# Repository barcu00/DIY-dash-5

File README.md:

# DIY Dash 5

DIY Dash 5 is an open, configurable auxiliary CAN dashboard for motorsport and
road cars. It is designed for the **Waveshare ESP32-S3-Touch-LCD-5 non-B**
board with an 800 × 480 RGB display, GT911 touch controller, 16 MB flash, and
8 MB OPI PSRAM.

The dashboard does not replace the factory instrument cluster. It adds a
dedicated screen for engine, ECU, and vehicle data, configurable warnings,
temperature status, and a track-oriented shift light. CAN operation is passive
and receive-only.

## Current firmware

The current test-board release is **v0.2.1**.

- [Open the v0.2.1 release](https://github.com/barcu00/DIY-dash-5/releases/tag/v0.2.1)
- [Download the complete 16 MB flash image](https://github.com/barcu00/DIY-dash-5/releases/download/v0.2.1/DIY-Dash-ESP32-S3-Touch-LCD-5-full.bin)
- [View the validated GitHub Actions build](https://github.com/barcu00/DIY-dash-5/actions/runs/34399159652)

Flash the complete image at address **`0x0`**. Its expected SHA-256 is:

```text
9FC9DD483754B7DDDF8EE3D20B1D87F31489FC43DA1D19DF0F165997BE9AAF70
```

> [!IMPORTANT]
> v0.2.1 is a prerelease for a physical test board. Automated tests verify the
> software, UI previews, ESP32-S3 compilation, and binary packaging. Vehicle
> wiring, touch response, CAN traffic, temperature, and long-duration stability
> still require validation on the actual installation.

## Development firmware: required storage migration

The current development build stores the complete dashboard configuration in
the dedicated **`dashcfg`** NVS partition. It is **512 KiB**, separate from the
small system NVS partition used by the ESP32 and Bluetooth stack. Every save is
read back byte-for-byte before the active configuration is changed.

This partition layout must be installed once with the merged image. Download
`DIY-Dash-ESP32-S3-Touch-LCD-5-full.bin` from the matching successful GitHub
Actions run and **flash at 0x0**. Installing this full image replaces the old
partition table and **clears existing settings**; configure the dashboard again
after the first boot. Do not install this migration using `firmware.bin` alone.
Later source builds remain fully compilable with PlatformIO as described below.

BACK, DASH, and TRACK all use the same deferred, verified save path. A failed
save keeps the current screen usable and shows `EXIT WITHOUT SAVE`, so the
driver can discard the draft instead of becoming trapped in `SAVE ERROR`.
RaceChrono now uses a 64 × 32 switch and separate status lines, including
`BLE: WAITING FOR APP`, `DATA: WAITING`/`DATA: ACTIVE`, and `GPS: NO FIX`.

## Interface preview

### Development: original selectable layouts

The `dashboard-dev` branch adds **Classic DASH, Classic TRACK, Analog Style,
Side Gear, and Strip Style**; newer builds add OEM Sport, Track Focus,
Endurance, Analog Classic, and Analog Twin (Modern Motorsport was removed in
configuration schema 12). In SETTINGS the layouts are now named FULL GRID,
TRACK GRID, DIAL + ROWS, GEAR LEFT, ARC STRIP, ROAD SPORT, LAP TIMER,
ENDURANCE, GAUGES and TWIN DIALS (same order as the names above). This is newer than the published v0.2.1 BIN above;
it is not yet a released firmware.

In `SETTINGS > LAYOUTS`, assign any preset independently to DASH and TRACK.
Each page retains its own tile settings for every preset. The shared
`RPM SCALE MAX` slider controls both pages from 100 to 10,000 RPM in 100-RPM
steps and does not change shift-light thresholds. Changes save on screen exit.
Hidden tiles compact within their group; holding a tile opens the existing
full-screen editor. Navigation includes gauge, checkered flag, and gear icons.

The development layouts below are **real production-view LVGL 8.4
framebuffer captures**, rendered on GitHub with the firmware's TileView,
RpmScaleView, ShiftLightView and navigation code. No UI reconstruction is used.
Black panels, condensed white digits, fine blue-grey frames and cyan navigation
follow the approved visual prototypes. Analog D uses a colored ring, a moving
white rectangular index and a configurable center tile (RPM by default).
Hold the center tile to choose a parameter, visibility and warning settings;
the ring and index always remain RPM-driven. At the flash threshold, the entire
segmented ring flashes red/dim at 4 Hz while the index remains white.
Side Gear
shares one RPM/speed frame; Strip uses identical upright rectangular blocks without a logo.
Tile rails and frames are neutral grey, compact-row labels and values are optically centered, and
scale labels always use whole thousands. Physical performance still needs board testing.

| Analog Style | Side Gear | Strip Style |
| --- | --- | --- |
|  |  |  |

| DASH | TRACK |
| --- | --- |
|  |  |

The [production preview workflow](.github/workflows/production-view-previews.yml)
checks 18 scenes, including flags, warning borders, 6000/7500/10000 RPM, red flash
phases and unavailable captions. It compares incremental redraws against full
framebuffers for Analog, Side Gear and Strip, including small
RPM changes and validity transitions. Its artifacts provide all captured scenes.
Configuration schema v8 migrates v6/v7 settings while retaining the original
layout banks and warning-sound preference; the new layout starts with its own defaults.
The display now uses two complete RGB framebuffers with VSYNC-controlled swaps,
and a 512 KiB LVGL pool in PSRAM.
Returning from settings or a successful tile save prepares the destination
layout and current values before displaying it, avoiding a stale first frame.
See [UI transition and Analog validation](docs/ui/ui-transition-validation.md)
for the successful build, full-image checksum and flashing precautions.
The newer [RGB/NVS XIP test candidate](docs/ui/rgb-nvs-xip-validation.md)
uses the official Arduino 3.1.1-h SDK libraries to support RGB bounce-buffer
operation during flash saves. Its GitHub tests and target build passed; physical
save-time stability still requires board testing. SDK selection is automatic
through `platformio.ini`, with compile-time checks against incompatible libraries.
### Development: tabbed editor and shared RPM settings

The new full-screen editor offers DATA, WARNING and temperature-only TEMPERATURE
BAR tabs, a large numeric keypad, and a categorized capability-filtered parameter
picker. Warning settings use an explicit RESET BELOW/ABOVE boundary. Untouched
fields retain native precision when saving in PSI, kPa or Fahrenheit.
TEST WARNING previews the modal and optionally pulses the buzzer without changing
actual alarms. RPM & SHIFT LIGHT combines the shared scale, color/flash thresholds,
a clearly labelled `12-LED FILL MAX` slider and one FLASH ENABLED switch. Fill max
sets the RPM at which all 12 segments are lit; it is no longer an isolated lower-right
field. Settings still save on exit;
tile drafts commit only after successful storage. SDK XIP and VSYNC buffering remain unchanged.

These are **actual production LVGL captures**, validated in direct and partial
render modes. See [candidate tests, checksum and hardware checklist](docs/ui/tile-editor-rpm-validation.md).

| DATA | WARNING | TEMPERATURE BAR |
| --- | --- | --- |
|  |  |  |

| NUMERIC ENTRY | PARAMETER PICKER | RPM & SHIFT LIGHT |
| --- | --- | --- |
|  |  |  |

The settings/flag/modal illustrations below remain older geometry previews,
not current production editor captures.

| SETTINGS | TILE SETTINGS |
| --- | --- |
|  |  |

| STATUS FLAGS | WARNING MODAL |
| --- | --- |
|  |  |

The real layout captures and earlier geometry previews are available in
[`docs/ui/screenshots`](docs/ui/screenshots).

## Main features

### RaceChrono Bluetooth LE monitor (development)

The development firmware advertises as **`DIY DASH RC`** and implements the
RaceChrono DIY Monitor service `0x1FF8`. Enable it under
`SETTINGS > DATA & CAN > RACECHRONO`; the full-screen `CONNECTION` and
`CHANNELS` pages show live BLE/GPS state and all 33 supplemental channels.
**CAN / DEMO remains active** while RaceChrono adds lap time, live delta,
comparison/reference time, sector, GPS, satellite, accuracy, position, and
acceleration data. RaceChrono values can be selected for any compatible tile
even while the phone is disconnected, and unavailable values show `---`.

One-time RaceChrono app path:

```text
RaceChrono Settings
  Add other device
  RaceChrono DIY
  Bluetooth LE
  DIY DASH RC
  Monitor
```

RaceChrono initiates the connection after a session starts. The connection
screen reports `BLE: WAITING FOR APP` before the phone connects, then
`BLE: CONNECTED`; data and GPS are reported independently. See the complete
[RaceChrono setup guide](docs/racechrono/setup.md).

| CONNECTION | CHANNELS | RACECHRONO picker |
| --- | --- | --- |
|  |  |  |

Development firmware also supports an active 12 V warning buzzer on DO0: one
startup test chirp, intermittent unacknowledged-warning sound and a persistent
`SETTINGS > SYSTEM > WARNING SOUND` option. See [wiring and behavior](docs/hardware/warning-buzzer.md).
This is not included in the older published v0.2.1 BIN.

### Configurable DASH and TRACK pages

- DASH has four small tiles on the left, four on the right, two centered wide
  tiles, and four center-small tiles.
- TRACK has four small tiles on each side and four centered wide tiles.
- Hiding a tile compacts only its logical column or group downward.
- Wide-tile labels and values remain centered.
- Holding a visible tile for approximately 600 ms opens its independent,
  full-screen editor. A short tap does not open it.
- Hidden tiles can be restored from `SETTINGS > LAYOUTS`.
- Every tile stores its parameter, visibility, decimals, warning, temperature
  bar configuration, and flag color independently in NVS.

### Smooth live data

- The visible data page renders at a stable 40 Hz cadence.
- Fast parameters update at 40 Hz, medium parameters at 20 Hz, and slow
  parameters at 10 Hz.
- Numeric presentation interpolates between incoming samples where appropriate.
- Warning and shift-light decisions use raw telemetry at 200 Hz and are not
  delayed by display interpolation.
- DEMO uses a smooth repeatable engine cycle, including a two-second RPM hold
  at 7800 RPM.

### Per-tile warnings

Each numeric tile can independently configure:

- enabled or disabled;
- activation above or below the threshold;
- native threshold from `0.0` to `999.0`;
- native hysteresis from `0.0` to `999.0` (development UI edits its reset boundary);
- delay from 0 to 10000 ms.

When a limit is exceeded for the configured delay, the UI opens a large red
`WARNING` modal with the parameter name, current value, configured limit, and
the number of additional active warnings. Acknowledging the modal leaves the
related tile highlighted until the signal returns through its hysteresis
boundary. Hidden tiles can still raise warnings.

Changing a numeric tile parameter clears the previous parameter's stale warning.
A new warning configured afterward in the same editor session is preserved.
Warnings are disabled by default in DEMO and must be enabled for the selected
tile when testing this function.

### Temperature bars

Temperature tiles can display a thin continuous colored bar. Each tile has four
temperature controls (development UI edits them in the selected display unit):

| Control | Meaning |
| --- | --- |
| `MIN` | Empty end of the fill scale |
| `READY` | Start of the normal operating range |
| `RED` | Independent red over-temperature threshold |
| `MAX` | Full end of the fill scale |

The required order is `MIN < READY < RED <= MAX`. Native temperature limits
support `-999.0` to `999.0`; the development keypad uses normal decimal notation.

- blue: below READY;
- green: normal range;
- yellow: final quarter of the READY-to-RED interval;
- red: at or above RED;
- empty: invalid or unavailable data.

Coolant and oil temperature bars start enabled with default values
`+040.0 / +075.0 / +115.0 / +130.0 °C`. IAT, fuel temperature, and EGT bars
have parameter-specific defaults but start disabled.

### Shift light

DASH and TRACK share the same 12-segment shift-light strip:

- four green segments;
- four yellow segments;
- four red segments;
- adjustable `START`, `RED`, `FLASH`, and `MAX` thresholds;
- 0 to 10000 RPM range in 100 RPM steps;
- required order `START < RED < FLASH <= MAX`;
- optional full-strip red flashing at approximately 4 Hz above `FLASH`.

### Fixed SETTINGS screens

SETTINGS uses separate non-scrolling 800 × 480 screens to keep touch and redraw
performance predictable:

| Category | Functions |
| --- | --- |
| DISPLAY | Software brightness from 20% to 100% |
| DATA & CAN | Explicit DEMO/CAN source, ECU profile, bitrate, and timeout |
| RPM & SHIFT LIGHT (development) | Shared scale, color/flash sliders, keypad and flash enable switch |
| UNITS | Temperature, pressure, speed, lambda/AFR, and stoichiometric AFR |
| LAYOUTS | Paged DASH/TRACK slot list and hidden-tile restoration |
| SYSTEM | Runtime information, layout reset, and factory reset |

Settings are changed in RAM while the controls are used and written once when
the user leaves the settings screen. Tile settings use `SAVE TILE` and update
the runtime only after persistent storage confirms a successful write.

## Telemetry and selectable data

`VehicleState` plus the independent RaceChrono overlay are the common sources
used by DEMO, CAN profiles, warnings, and the UI. The current registry contains
**134 selectable parameters**:

- 35 numeric measurements;
- 66 boolean or status flags;
- 33 RaceChrono lap, sector, GPS, position, and acceleration channels.

Numeric data includes RPM, speed, gear, throttle, MAP/boost, lambda, coolant,
oil and intake temperatures, oil/fuel/coolant pressure, battery voltage,
barometric pressure, ethanol content, ignition, injection, airflow, EGT 1–8,
and individual wheel speeds.

DEMO exposes the complete registry. CAN exposes only parameters substantiated
by the selected compiled profile. If a saved tile is not supported by a newly
selected profile, its assignment remains stored and the UI shows `---` or
`UNAVAILABLE` instead of inventing a value.

Boolean tiles show a neutral grey `OFF` state. When active, they use the
per-tile yellow, green, or red color selected by the user. Invalid or stale
flags show `UNAVAILABLE` and never retain the active color.

## CAN profiles

| Profile | Status | Default bitrate | Implemented scope |
| --- | --- | ---: | --- |
| ECUMaster EMU Black | Verified | 1000 kbit/s | Official `0x600–0x607` stream, numeric data and documented states |
| rusEFI verbose | Verified | 500 kbit/s | Official verbose CAN frames, extended engine data and states |
| MaxxECU Default 1.3 | Verified | 500 kbit/s | Official default protocol, extended numeric data and states |
| Haltech Broadcast 2.0 | Verified | 1000 kbit/s | Official big-endian broadcast numeric channels |
| Speeduino Haltech mode | Verified | 500 kbit/s | Populated Haltech-compatible Speeduino channels |
| BMW MS43 Stock | Verified | 500 kbit/s | Stock `0x316`, `0x329`, and `0x545` powertrain frames and verified states |
| Link Generic Dash | Experimental | 1000 kbit/s | Generic Dash frame `0x3E8`; ECU transmission must be configured |
| PSA Citroën C2 VTS engine | Experimental | 500 kbit/s | HS.IS `0x208` and `0x488`; RPM, TPS, CLT, oil and intake temperature |

The BMW profile is stock and passive. It does not require an OLM or K-line
patch and does not use a custom `0x33C` stream. The PSA profile uses engine CAN
only and intentionally excludes VAN, diagnostics, ABS, and uncertain signals.

Exact protocol sources, revisions, frame IDs, mapped channels, and verification
boundaries are recorded in the
[`CAN Profile Source Ledger`](docs/can/profile-sources.md).

## Required hardware

- Waveshare ESP32-S3-Touch-LCD-5 **non-B**;
- USB data cable for programming and serial diagnostics;
- correctly powered display board;
- correctly terminated CAN bus;
- CANH, CANL, and a shared electrical ground with the vehicle/ECU.

CAN/TWAI pin assignment used by the firmware:

| Function | ESP32-S3 GPIO |
| --- | ---: |
| CAN TX | GPIO15 |
| CAN RX | GPIO16 |

> [!CAUTION]
> Confirm voltage levels, grounding, termination, and connector pinout before
> connecting the dashboard to a vehicle. The firmware uses receive-only CAN,
> but incorrect electrical wiring can still damage the board or other modules.

## Install the ready-to-use firmware

### Method 1 — GitHub Release and complete BIN (recommended)

This method does not require downloading or compiling the source code.

1. Download
   [`DIY-Dash-ESP32-S3-Touch-LCD-5-full.bin`](https://github.com/barcu00/DIY-dash-5/releases/download/v0.2.1/DIY-Dash-ESP32-S3-Touch-LCD-5-full.bin).
2. Install Python 3 and Espressif's flashing tool:

   ```bash
   python -m pip install --upgrade esptool
   ```

3. Connect the ESP32-S3 board by USB and identify its serial port.
4. Erase the target flash:

   ```bash
   python -m esptool --chip esp32s3 --port COM5 erase_flash
   ```

5. Flash the complete image at `0x0`:

   ```bash
   python -m esptool --chip esp32s3 --port COM5 --baud 921600 write_flash \
     0x0 DIY-Dash-ESP32-S3-Touch-LCD-5-full.bin
   ```

> [!WARNING]
> `erase_flash` followed by the full image also erases the `dashcfg`
> partition: dashboard settings **and the odometer** return to defaults.
> Use it for a first installation or a clean start only.

### Updating an installed dash (keeps settings and odometer)

Flash only the application image at the app offset, without `erase_flash`:

```bash
python -m esptool --chip esp32s3 --port COM5 --baud 921600 write_flash \
  0x10000 DIY-Dash-ESP32-S3-Touch-LCD-5-app-update.bin
```

The offset is also recorded as `app_update_image` in `flash-layout.json`.
Before a clean install you can note the odometer value in
SETTINGS > ODOMETER & TRIP and restore it there with SET VALUE.

Replace `COM5` with the board port. On Linux it is commonly similar to
`/dev/ttyACM0` or `/dev/ttyUSB0`; on macOS it is commonly under `/dev/cu.*`.
If the board does not enter download mode automatically, use its BOOT/RESET
procedure and retry.

### Method 2 — GitHub Actions artifact

Every push and pull request runs the complete firmware workflow:

1. Open [GitHub Actions](https://github.com/barcu00/DIY-dash-5/actions/workflows/build-firmware.yml).
2. Select a successful run for the required commit.
3. Download the `DIY-Dash-firmware` artifact.
4. Extract it and flash the included full BIN at `0x0` using Method 1.

Actions artifacts are temporary development builds. For ordinary installation,
use the permanent full BIN attached to the v0.2.1 release. Release pages contain
only the complete ready-to-flash image; component binaries remain development
outputs inside Actions artifacts and local PlatformIO builds.

## Download, compile, and upload the complete project

The repository is a complete PlatformIO project. It can be cloned with Git or
downloaded as a ZIP, opened directly in PlatformIO, compiled without manually
installing Arduino libraries, and uploaded to the ESP32-S3 over USB. Required
libraries and their pinned versions are declared in [`platformio.ini`](platformio.ini).

### PlatformIO IDE in Visual Studio Code

1. Install [Visual Studio Code](https://code.visualstudio.com/).
2. Install the **PlatformIO IDE** extension.
3. Download the repository:
   - use `git clone https://github.com/barcu00/DIY-dash-5.git`, or
   - choose **Code > Download ZIP** on GitHub and extract the complete archive.
4. In VS Code select **File > Open Folder** and open the directory containing
   `platformio.ini`.
5. Wait for PlatformIO to install the pinned ESP32 platform and libraries.
6. Select the `waveshare_5` environment.
7. Use **PlatformIO: Build** to compile the complete software.
8. Connect the board and use **PlatformIO: Upload** to flash it.

Generated files are placed in `.pio/build/waveshare_5/`, including:

- `firmware.bin`;
- `bootloader.bin`;
- `partitions.bin`;
- `DIY-Dash-ESP32-S3-Touch-LCD-5-full.bin`;
- `flash-layout.json`.

### PlatformIO command line

```bash
git clone https://github.com/barcu00/DIY-dash-5.git
cd DIY-dash-5
python -m pip install platformio==6.1.18
pio run -e waveshare_5
pio run -e waveshare_5 -t upload --upload-port COM5
```

To run the complete native regression suite before the ESP32 build:

```bash
pio test -e native
```

Replace `COM5` with the detected ESP32-S3 port. The build post-script creates
the merged 16 MB image and flash layout from PlatformIO's actual build metadata.

## First start and configuration

1. After flashing, reset or power-cycle the board.
2. Confirm that DASH appears at 800 × 480 and touch navigation works.
3. Open `SETTINGS > DATA & CAN`.
4. Select `DEMO` for UI testing, or select `CAN` and the matching ECU profile.
5. Set the required CAN bitrate and timeout.
6. Leave the settings page to save the configuration.
7. Hold a tile to configure its parameter, warning, visibility, decimal count,
   temperature bar, or flag color.
8. Test warnings in DEMO by enabling a warning and choosing a threshold crossed
   by the generated signal range.

CAN mode never silently falls back to DEMO. A disconnected, invalid, or stale
CAN signal is displayed as unavailable.

## Software architecture

```text
ESP32 TWAI / CAN frames
        │
        ▼
    CanDriver
        │
        ▼
Table-driven ECU decoder ──────── DEMO telemetry
        │                              │
        └──────────► VehicleState ◄────┘
                         │
             ┌───────────┼───────────┐
             ▼           ▼           ▼
       Tile warnings  Shift light  LVGL tile views
             │           │           │
             └───────────┴───────────┘
                         │
                         ▼
                  800 × 480 display
```

Hardware-specific display, touch, and CAN access are isolated from the native
C++ telemetry, configuration, decoder, warning, and presentation models. CAN
definitions remain table-driven; raw byte layouts do not leak into UI code.

## Build and verification status

The current v0.2.1 firmware was built from commit
[`5d561ed`](https://github.com/barcu00/DIY-dash-5/commit/5d561edc4229067916ff45e37cbaf7651880f462).

| Check | Result |
| --- | ---: |
| Native test cases | 176 / 176 passed |
| Push workflow | [Passed](https://github.com/barcu00/DIY-dash-5/actions/runs/34399159652) |
| Pull-request workflow | [Passed](https://github.com/barcu00/DIY-dash-5/actions/runs/34399164683) |
| Static RAM | 131,656 / 327,680 bytes — 40.2% |
| Application flash | 711,144 / 6,553,600 bytes — 10.9% |
| Complete flash image | 16,777,216 bytes |

GitHub Actions performs:

1. 176 native C++ tests;
2. Python packaging and UI contract tests;
3. Waveshare ESP32-S3 firmware compilation;
4. deterministic rendering of all UI previews;
5. merged BIN and flash-layout generation;
6. firmware artifact upload.

## Software stack

- C++17;
- PlatformIO 6.1.18;
- pioarduino ESP32 platform 53.3.11 / Arduino-ESP32 3.1.1;
- LVGL 8.4.0;
- ESP32_Display_Panel 1.0.4;
- ESP32_IO_Expander 1.1.1;
- esp-lib-utils 0.2.0.

Versions are pinned in [`platformio.ini`](platformio.ini) to keep CI and
developer builds reproducible.

## Repository map

| Path | Purpose |
| --- | --- |
| `src/app` | Runtime orchestration |
| `src/board` | RGB display, GT911 touch, brightness, and diagnostics |
| `src/can` | ESP32 TWAI receive-only driver |
| `src/ecu` | CAN profiles and table-driven decoding |
| `src/telemetry` | Parameter registry, DEMO data, and `VehicleState` |
| `src/racechrono` | RaceChrono Monitor protocol, session, telemetry, and BLE transport |
| `src/alarms` | Per-tile warning state machine |
| `src/settings` | Defaults, validation, schema migration, and NVS storage |
| `src/ui` | Layout, editor, settings, tiles, shift light, and presentation |
| `test` | Native regression and protocol fixture tests |
| `scripts` | Firmware packaging, UI rendering, and contract tests |
| `docs/can` | Profile source ledger and mapping boundaries |
| `docs/ui` | User guide and current screen previews |

## Current limitations

- This is not yet a production-certified automotive instrument.
- The non-B Waveshare board is the only current hardware target.
- Link Generic Dash and PSA C2 mappings remain experimental until verified
  against captured traffic from the exact target vehicle/ECU.
- The firmware does not implement BMW MS43 OLM, a custom `0x33C` stream, or
  K-line acquisition.
- The PSA profile does not decode VAN traffic.
- microSD logging and profile import/export are not implemented in v0.2.1.
- RaceChrono BLE hardware acceptance is pending on a physical phone and board.
- CI cannot validate electrical wiring, display timing under every condition,
  vehicle-bus compatibility, or long-duration thermal stability.

## Physical-board acceptance checklist

After flashing, verify:

1. the board boots without a reset loop;
2. DASH renders at the full 800 × 480 resolution;
3. touch switches between DASH, TRACK, and every SETTINGS category;
4. long-press opens a tile editor while a short tap does nothing;
5. DEMO data, temperature bars, warnings, and the shift light behave correctly;
6. repeated slider and brightness interaction causes no artifacts;
7. saved settings survive a restart;
8. CAN changes from waiting/offline only after receiving a mapped frame;
9. disconnecting CAN invalidates stale values and never activates DEMO;
10. the display remains responsive during a minimum 15-minute test.

## Documentation

- [Dashboard configuration guide](docs/ui/dashboard-config-guide.md)
- [RaceChrono Bluetooth LE setup](docs/racechrono/setup.md)
- [CAN profile source ledger](docs/can/profile-sources.md)
- [Current v0.2.1 release](https://github.com/barcu00/DIY-dash-5/releases/tag/v0.2.1)
- [GitHub Actions firmware workflow](.github/workflows/build-firmware.yml)

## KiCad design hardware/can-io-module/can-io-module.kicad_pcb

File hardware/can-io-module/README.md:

# DIY Dash 5 CAN I/O module

This KiCad 9 project is a low-cost, external automotive sensor and gateway module for DIY Dash 5. It combines eight configurable analog/resistive inputs, a Type-K EGT channel, Flex Fuel capture, BMW MS43 K-line, CAN, two 0–5 V signal outputs, and two protected low-side relay outputs.

## 24-pin connector

| Pin | Signal | Pin | Signal | Pin | Signal |
| ---: | --- | ---: | --- | ---: | --- |
| 1 | VBAT | 9 | AIN1 | 17 | EGT_K_POS |
| 2 | POWER_GND | 10 | AIN2 | 18 | EGT_K_NEG |
| 3 | IGN | 11 | AIN3 | 19 | RELAY_OUT1 |
| 4 | CAN_H | 12 | AIN4 | 20 | RELAY_OUT2 |
| 5 | CAN_L | 13 | AIN5 | 21 | FLEX_IN |
| 6 | K_LINE | 14 | AIN6 | 22 | AOUT1 |
| 7 | SENSOR_5V | 15 | AIN7 | 23 | AOUT2 |
| 8 | SENSOR_GND | 16 | AIN8 | 24 | SERVICE |

The analog outputs are only for ECU/logger inputs of at least 10 kOhm. Relay outputs are limited to 500 mA continuous each. This module is not a safety controller.

## Validation

GitHub Actions installs KiCad 9, runs the Python design contract, ERC, DRC with schematic parity, schematic PDF and PCB SVG exports, position export, and Gerber/drill generation. The canonical commands are in `.github/workflows/can-io-hardware.yml`; `scripts/export_can_io_hardware.ps1` mirrors them for a workstation with KiCad 9.

Fabrication outputs are prototypes only. Do not order a production batch until the exact purchased connector and enclosure have passed the mechanical fit gate described in `manufacturing/prototype-fabrication-notice.txt`.

## Current design maturity

Revision A is an engineering architecture and placement prototype. KiCad 9 parses it, ERC is clean, and the board has a closed outline, fixed connector mapping, functional placement zones, keep-outs, a ground plane, and an auditable BOM. Major electronic footprints are presently placement blocks and the schematic sheets document the circuit architecture rather than a production netlist. Therefore this revision is **not electrically fabrication-ready** and must not be described as a fully routed production PCB. The complete symbol-level circuit, real package footprints, routed nets, thermal review, enclosure measurements, and bench validation remain release gates.

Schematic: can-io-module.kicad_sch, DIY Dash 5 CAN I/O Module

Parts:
C1: 10uF 50V input; 1210
C2: 22uF 10V buck output; 1206
C3: 4.7uF 10V 3V3 bulk; 0805
C4: 100nF U1 VDD1; 0603
C5: 100nF U1 VDD2; 0603
C6: 100nF U1 VDDA; 0603
C7: 100nF buck bootstrap; 0603
C8: 10nF VBAT monitor filter; 0603
C9: 10nF 5V monitor filter; 0603
C10: 10nF 3V3 monitor filter; 0603
C11: 10nF IGN sense filter; 0603
C101, C102, C103, C104, C105, C106, C107, C108: 100nF ADC filter; 0603
D1: SMBJ33A; SMB_DO-214AA
D2: Buck catch diode 60V; SMA_DO-214AC
D3: CAN TVS; SOT23
D4: K-line TVS 24V; SMA_DO-214AC
D5: Flex TVS 5V; SOD323
D6: AOUT1 ESD; SOD323
D7: AOUT2 ESD; SOD323
F1: 1A input fuse; NANO2_2410
F2: 250mA resettable sensor fuse; 1206
FB1: 600R ferrite VDDA; 0603
J1: ECU_FCI_24P_RightAngle
J2: SWD_1x05_P2.54mm_DNP; SWD_1x05_P2.54mm_Vertical
JP1: 120R CAN termination; 0603
L1: 22uH buck inductor; 5.5x5.5mm
L2: CAN common-mode choke; 1812_common-mode
Q1: 60V P-channel reverse polarity; PowerPAK_SO-8
Q4: 60V logic N-MOS RELAY1; LFPAK56
Q5: 60V logic N-MOS RELAY2; LFPAK56
R1: 1.00k 1% excitation; 0603
R2: 4.70k 1% excitation; 0603
R3, R4: 100k mux enable safe-state; 0603
R5, R6: 100k relay gate pull-down; 0603
R7: 220R AOUT1 isolation; 0603
R8: 220R AOUT2 isolation; 0603
R9: 10k NRST pull-up; 0603
R10: 100k BOOT0 pull-down; 0603
R11: 40.2k 1% buck FB upper; 0603
R12: 10.0k 1% buck FB lower; 0603
R13: 100k 1% VBAT monitor upper; 0603
R14: 15.0k 1% VBAT monitor lower; 0603
R15: 10.0k 1% 5V monitor upper; 0603
R16: 18.0k 1% 5V monitor lower; 0603
R17: 1.00k 1% 3V3 monitor upper; 0603
R18: 100k 1% 3V3 monitor lower; 0603
R19: 100k 1% IGN sense upper; 0603
R20: 15.0k 1% IGN sense lower; 0603
R101, R102, R103, R104, R105, R106, R107, R108: 10.0k 1% AIN series; 0603
R111, R112, R113, R114, R115, R116, R117, R118: 15.0k 1% AIN lower; 0603
TP1: SWDIO; Test_pad
TP2: SWCLK; Test_pad
TP3: NRST; Test_pad
TVS11: AIN1 low-leakage ESD; SOD323
TVS12: AIN2 low-leakage ESD; SOD323
TVS13: AIN3 low-leakage ESD; SOD323
TVS14: AIN4 low-leakage ESD; SOD323
TVS15: AIN5 low-leakage ESD; SOD323
TVS16: AIN6 low-leakage ESD; SOD323
TVS17: AIN7 low-leakage ESD; SOD323
TVS18: AIN8 low-leakage ESD; SOD323
U1: STM32G0B1CBT6; LQFP-48_7x7mm
U2: LMR16006Y-Q1; SOT-23-THN-6_DDC
U3: 3V3 LDO 300mA; SOT-23-5
U4: SENSOR_5V load switch; SC70-5
U5: 74HCT4051 1K excitation; SOIC-16
U6: 74HCT4051 4K7 excitation; SOIC-16
U7: L9613; SO-8
U8: TJA1051T/3; SO-8_SOT96-1
U9: TLV9002-Q1; SOIC-8
U10: MAX31855KASA+; SOIC-8_narrow
U11: Schmitt Flex front end; SOT-353

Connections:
+3V3: C3.1, C4.1, C5.1, FB1.1, J2.1 (+3V3), R9.1, R17.1, U1.4, U1.6, U3.5, U8.5, U10.4, U11.5
+5V: C2.1, L1.2, R1.1, R2.1, R3.1, R4.1, R11.1, R15.1, U3.1, U3.3, U4.5, U5.16, U6.16, U7.3, U8.3, U9.8
ADC_IN1: C101.1, R101.2, R111.1, U1.11
ADC_IN2: C102.1, R102.2, R112.1, U1.12
ADC_IN3: C103.1, R103.2, R113.1, U1.13
ADC_IN4: C104.1, R104.2, R114.1, U1.14
ADC_IN5: C105.1, R105.2, R115.1, U1.17
ADC_IN6: C106.1, R106.2, R116.1, U1.18
ADC_IN7: C107.1, R107.2, R117.1, U1.19
ADC_IN8: C108.1, R108.2, R118.1, U1.20
AIN1: J1.9 (AIN1), R101.1, TVS11.1, U5.13, U6.13
AIN2: J1.10 (AIN2), R102.1, TVS12.1, U5.14, U6.14
AIN3: J1.11 (AIN3), R103.1, TVS13.1, U5.15, U6.15
AIN4: J1.12 (AIN4), R104.1, TVS14.1, U5.12, U6.12
AIN5: J1.13 (AIN5), R105.1, TVS15.1, U5.1, U6.1
AIN6: J1.14 (AIN6), R106.1, TVS16.1, U5.5, U6.5
AIN7: J1.15 (AIN7), R107.1, TVS17.1, U5.2, U6.2
AIN8: J1.16 (AIN8), R108.1, TVS18.1, U5.4, U6.4
AOUT1: D6.1, J1.22 (AOUT1), R7.2
AOUT1_OP: R7.1, U9.2, U9.3
AOUT2: D7.1, J1.23 (AOUT2), R8.2
AOUT2_OP: R8.1, U9.6, U9.7
BOOT0: R10.1, U1.21
BUCK_BOOT: C7.1, U2.1
BUCK_FB: R11.2, R12.1, U2.3
BUCK_SW: C7.2, D2.2, L1.1, U2.6
CAN_H: D3.1, J1.4 (CAN_H), JP1.1, L2.3
CAN_H_PROTECTED: L2.1, U8.7
CAN_L: D3.2, J1.5 (CAN_L), JP1.2, L2.4
CAN_L_PROTECTED: L2.2, U8.6
CAN_RX: U1.33, U8.4
CAN_SILENT: U1.26, U8.8
CAN_TX: U1.34, U8.1
DAC1_RAW: U1.15, U9.1
DAC2_RAW: U1.16, U9.5
EGT_CS: U1.44, U10.6
EGT_K_NEG: J1.18 (EGT_K_NEG), U10.3
EGT_K_POS: J1.17 (EGT_K_POS), U10.2
EGT_SCK: U1.42, U10.5
EGT_SO: U1.43, U10.7
EXC_1K: R1.2, U5.3
EXC_4K7: R2.2, U6.3
FLEX_CAPTURE: U1.28, U11.4
FLEX_IN: D5.1, J1.21 (FLEX_IN), U11.2
IGN: J1.3 (IGN), Q1.1, R19.1, U2.4
IGN_SENSE: C11.1, R19.2, R20.1, U1.29
KRX: U1.46, U7.1
KTX: U1.45, U7.4
K_LINE: D4.1, J1.6 (K_LINE), U7.6
NRST: J2.4 (NRST), R9.2, TP3.1, U1.10
POWER_GND: C1.2, C2.2, C3.2, C4.2, C5.2, C6.2, C8.2, C9.2, C10.2, C11.2, D1.2, D2.1, D4.2, D5.2, D6.2, D7.2, J1.2 (POWER_GND), J2.5 (POWER_GND), Q4.3, Q5.3, R5.2, R6.2, R10.2, R12.2, R14.2, R16.2, R18.2, R20.2, TVS11.2, TVS12.2, TVS13.2, TVS14.2, TVS15.2, TVS16.2, TVS17.2, TVS18.2, U1.7, U2.2, U3.2, U4.2, U5.7, U5.8, U6.7, U6.8, U7.5, U8.2, U9.4, U10.1, U11.3
PULL_1K_EN_N: R3.2, U1.41, U5.6
PULL_4K7_EN_N: R4.2, U1.30, U6.6
PULL_A0: U1.38, U5.11, U6.11
PULL_A1: U1.39, U5.10, U6.10
PULL_A2: U1.40, U5.9, U6.9
RELAY1_GATE: Q4.1, R5.1, U1.31
RELAY2_GATE: Q5.1, R6.1, U1.25
RELAY_OUT1: J1.19 (RELAY_OUT1), Q4.2, Q4.4, Q4.5, Q4.6, Q4.7, Q4.8
RELAY_OUT2: J1.20 (RELAY_OUT2), Q5.2, Q5.4, Q5.5, Q5.6, Q5.7, Q5.8
SENSOR_5V: F2.2, J1.7 (SENSOR_5V)
SENSOR_5V_EN: U1.27, U4.4
SENSOR_5V_OC: U1.47, U4.3
SENSOR_5V_SW: F2.1, U4.1
SENSOR_GND: C101.2, C102.2, C103.2, C104.2, C105.2, C106.2, C107.2, C108.2, J1.8 (SENSOR_GND), R111.2, R112.2, R113.2, R114.2, R115.2, R116.2, R117.2, R118.2
SERVICE: J1.24 (SERVICE), U1.32
SWCLK: J2.3 (SWCLK), TP2.1, U1.36
SWDIO: J2.2 (SWDIO), TP1.1, U1.35
V3V3_MON: C10.1, R17.2, R18.1, U1.24
V5_MON: C9.1, R15.2, R16.1, U1.23
VBAT: F1.1, J1.1 (VBAT)
VBAT_FUSED: F1.2, Q1.3, Q1.4
VBAT_MON: C8.1, R13.2, R14.1, U1.22
VBAT_PROTECTED: C1.1, D1.1, Q1.2, R13.1, U2.5, U7.7
VDDA: C6.1, FB1.2, U1.5

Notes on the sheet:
CAN I/O MODULE - ELECTRICAL SOURCE OF TRUTH
Every net label is wired to the numbered physical package pin. J2: 1 +3V3, 2 SWDIO, 3 SWCLK, 4 NRST, 5 POWER_GND.
J1 / Custom THT 3x8
J2 / PinHeader_1x05_P2.54mm_Vertical
U1 / LQFP-48 7x7mm
U2 / SOT-23-THN-6 DDC
U3 / SOT-23-5
U4 / SC70-5
U5 / SOIC-16
U6 / SOIC-16
U7 / SO-8
U8 / SO-8 SOT96-1
U9 / SOIC-8
U10 / SOIC-8 narrow
U11 / SOT-353
Q1 / PowerPAK SO-8
Q4 / LFPAK56
Q5 / LFPAK56
D1 / SMB DO-214AA
D2 / SMA DO-214AC
D3 / SOT23
D4 / SMA DO-214AC
D5 / SOD323
D6 / SOD323
D7 / SOD323
JP1 / 0603
L1 / 5.5x5.5mm
L2 / 1812 common-mode
R1 / 0603
R2 / 0603
R3 / 0603
R4 / 0603
R5 / 0603
R6 / 0603
R7 / 0603
R8 / 0603
R9 / 0603
R10 / 0603
C1 / 1210
C2 / 1206

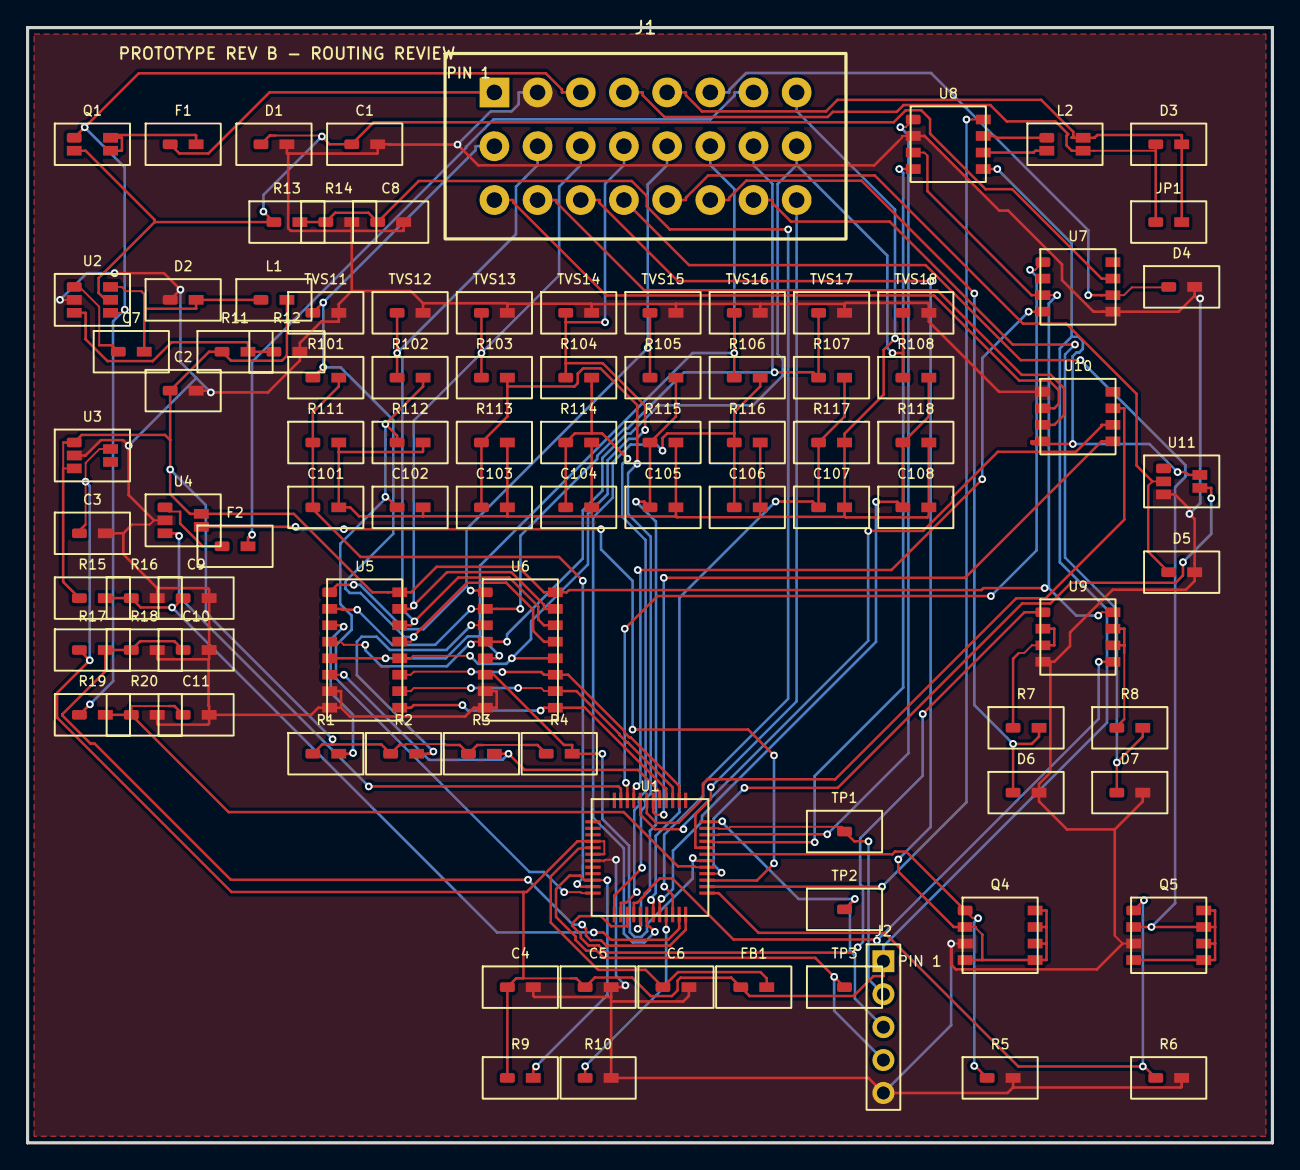
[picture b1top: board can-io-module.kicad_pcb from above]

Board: 2 copper layers, 96.0 x 86.0 mm, 95 parts (0 on the bottom side), 75 nets.

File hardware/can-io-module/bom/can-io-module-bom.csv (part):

Reference,Quantity,Value,Manufacturer,MPN,Package,Populate,Notes
J1,1,"ECU_FCI_24P_RightAngle","Generic",SOURCE_WITH_ENCLOSURE,Custom THT 3x8,YES,"Physical sample and 1:1 fit check mandatory"
J2,1,SWD_1x05_P2.54mm_DNP,Generic,61300511121,PinHeader_1x05_P2.54mm_Vertical,DNP,"Standard 2.54mm SWD service header; pin 1 marked"
U1,1,STM32G0B1CBT6,"STMicroelectronics",STM32G0B1CBT6,LQFP-48 7x7mm,YES,"Industrial -40..85C selected low-cost MCU"
U2,1,LMR16006Y-Q1,"Texas Instruments",LMR16006YQDDCRQ1,SOT-23-THN-6 DDC,YES,60V 600mA automotive buck
U3,1,3V3 LDO 300mA,"Texas Instruments",TPS7A2033PDBVR,SOT-23-5,YES,"Low-noise 3.3V rail"
U4,1,SENSOR_5V load switch,"Texas Instruments",TPS22945DCKR,SC70-5,YES,"Current-limited external sensor rail"
U5,1,"74HCT4051 1K excitation","Texas Instruments",CD74HCT4051M96,SOIC-16,YES,TTL thresholds accept 3.3V MCU at 5V supply
U6,1,"74HCT4051 4K7 excitation","Texas Instruments",CD74HCT4051M96,SOIC-16,YES,TTL thresholds accept 3.3V MCU at 5V supply
U7,1,L9613,"STMicroelectronics",L9613B013TR,SO-8,YES,"Fixed K-line transceiver; stock 9.6k and patched up to 125k"
U8,1,TJA1051T/3,NXP,TJA1051T/3/1J,SO-8 SOT96-1,YES,"VIO supports direct 3.3V MCU interface"
U9,1,TLV9002-Q1,"Texas Instruments",TLV9002QDRQ1,SOIC-8,YES,5V RRIO dual op amp
U10,1,MAX31855KASA+,"Analog Devices",MAX31855KASA+,"SOIC-8 narrow",YES,"Type-K -200C..1350C converter"
U11,1,"Schmitt Flex front end",Nexperia,"74LVC1G17GW,125",SOT-353,YES,"5V tolerant Schmitt input at 3.3V"
Q1,1,"60V P-channel reverse polarity",Vishay,SQJ461EP-T1_GE3,PowerPAK SO-8,YES,"Verify footprint thermal pad before order"
Q4,1,60V logic N-MOS RELAY1,Nexperia,"BUK9Y12-60E,115",LFPAK56,YES,Low-side 500mA maximum
Q5,1,60V logic N-MOS RELAY2,Nexperia,"BUK9Y12-60E,115",LFPAK56,YES,Low-side 500mA maximum
D1,1,SMBJ33A,"Diodes Incorporated",SMBJ33A-13-F,SMB DO-214AA,YES,"VBAT load-dump clamp; validate transient energy"
D2,1,Buck catch diode 60V,"Diodes Incorporated",B360A-13-F,SMA DO-214AC,YES,3A Schottky
D3,1,CAN TVS,Nexperia,PESD2CANFD24V-T,SOT23,YES,"Two-line automotive CAN protection"
D4,1,"K-line TVS 24V","Diodes Incorporated",SMAJ24CA-13-F,SMA DO-214AC,YES,"Bidirectional connector-side protection"
D5,1,Flex TVS 5V,Nexperia,"PESD5V0U1BA,115",SOD323,YES,"Low-capacitance connector protection"
D6,1,AOUT1 ESD,Nexperia,"PESD5V0U1BA,115",SOD323,YES,"Connector-side ESD"
D7,1,AOUT2 ESD,Nexperia,"PESD5V0U1BA,115",SOD323,YES,"Connector-side ESD"
JP1,1,"120R CAN termination",Yageo,RC0603FR-07120RL,0603,DNP,"Default open; populate only at bus end"
L1,1,"22uH buck inductor",Coilcraft,XAL5030-223MEB,5.5x5.5mm,YES,">=1.2A saturation and automotive temperature"
L2,1,"CAN common-mode choke",TDK,ACT45B-510-2P-TL003,"1812 common-mode",DNP,"Optional after EMC test; bypass links fitted"
R1,1,"1.00k 1% excitation",Yageo,RC0603FR-071KL,0603,YES,"0.1% preferred for resistance accuracy"
R2,1,"4.70k 1% excitation",Yageo,RC0603FR-074K7L,0603,YES,0.1% preferred for NTC accuracy
R3,1,"100k mux enable safe-state",Yageo,RC0603FR-07100KL,0603,YES,U5 reset disable pull-up to 5V
R4,1,"100k mux enable safe-state",Yageo,RC0603FR-07100KL,0603,YES,U6 reset disable pull-up to 5V
R5,1,"100k relay gate pull-down",Yageo,RC0603FR-07100KL,0603,YES,Relay 1 reset off
R6,1,"100k relay gate pull-down",Yageo,RC0603FR-07100KL,0603,YES,Relay 2 reset off
R7,1,"220R AOUT1 isolation",Yageo,RC0603FR-07220RL,0603,YES,"Short-current isolation"
R8,1,"220R AOUT2 isolation",Yageo,RC0603FR-07220RL,0603,YES,"Short-current isolation"
R9,1,10k NRST pull-up,Yageo,RC0603FR-0710KL,0603,YES,MCU reset
R10,1,"100k BOOT0 pull-down",Yageo,RC0603FR-07100KL,0603,YES,Normal boot default
C1,1,"10uF 50V input",Murata,GRM32ER71H106KA12L,1210,YES,"VBAT protected input bulk"
C2,1,22uF 10V buck output,Murata,GRM31CR61A226ME15L,1206,YES,5V rail
C3,1,4.7uF 10V 3V3 bulk,Murata,GRM21BR61A475KA73L,0805,YES,3V3 rail
C4,1,"100nF U1 VDD1",Murata,GRM188R71C104KA01D,0603,YES,"Place at pin"
C5,1,"100nF U1 VDD2",Murata,GRM188R71C104KA01D,0603,YES,"Place at pin"
C6,1,"100nF U1 VDDA",Murata,GRM188R71C104KA01D,0603,YES,"Place at pin"
C7,1,100nF buck bootstrap,Murata,GRM188R71H104KA93D,0603,YES,"LMR16006 CB-to-SW bootstrap capacitor"
C8,1,10nF VBAT monitor filter,Murata,GRM188R71H103KA01D,0603,YES,VBAT_MON low-pass filter
C9,1,10nF 5V monitor filter,Murata,GRM188R71H103KA01D,0603,YES,V5_MON low-pass filter
C10,1,10nF 3V3 monitor filter,Murata,GRM188R71H103KA01D,0603,YES,V3V3_MON low-pass filter
C11,1,10nF IGN sense filter,Murata,GRM188R71H103KA01D,0603,YES,IGN_SENSE low-pass filter
R11,1,40.2k 1% buck FB upper,Yageo,RC0603FR-0740K2L,0603,YES,LMR16006 5V feedback upper
R12,1,10.0k 1% buck FB lower,Yageo,RC0603FR-0710KL,0603,YES,LMR16006 5V feedback lower
R13,1,100k 1% VBAT monitor upper,Yageo,RC0603FR-07100KL,0603,YES,VBAT monitor divider upper
R14,1,15.0k 1% VBAT monitor lower,Yageo,RC0603FR-0715KL,0603,YES,VBAT monitor divider lower
R15,1,10.0k 1% 5V monitor upper,Yageo,RC0603FR-0710KL,0603,YES,5V monitor divider upper
R16,1,18.0k 1% 5V monitor lower,Yageo,RC0603FR-0718KL,0603,YES,5V monitor divider lower
R17,1,1.00k 1% 3V3 monitor upper,Yageo,RC0603FR-071KL,0603,YES,3V3 monitor divider upper
R18,1,100k 1% 3V3 monitor lower,Yageo,RC0603FR-07100KL,0603,YES,3V3 monitor divider lower
R19,1,100k 1% IGN sense upper,Yageo,RC0603FR-07100KL,0603,YES,IGN sense divider upper
R20,1,15.0k 1% IGN sense lower,Yageo,RC0603FR-0715KL,0603,YES,IGN sense divider lower
FB1,1,600R ferrite VDDA,Murata,BLM18PG601SN1D,0603,YES,"Analog rail filtering"
F1,1,"1A input fuse",Littelfuse,0451001.MRL,NANO2 2410,YES,"PCB protection; harness fuse still required"
F2,1,"250mA resettable sensor fuse",Littelfuse,1206L025YR,1206,YES,SENSOR_5V limit backup
TP1,1,SWDIO,"Keystone",5015,Test pad,YES,"Unpopulated service pad"
TP2,1,SWCLK,"Keystone",5015,Test pad,YES,"Unpopulated service pad"
TP3,1,NRST,"Keystone",5015,Test pad,YES,"Unpopulated service pad"
TVS11,1,AIN1 low-leakage ESD,Nexperia,"PESD3V3L1BA,115",SOD323,YES,"At connector"
R101,1,10.0k 1% AIN series,Yageo,RC0603FR-0710KL,0603,YES,AIN1 divider upper
R111,1,15.0k 1% AIN lower,Yageo,RC0603FR-0715KL,0603,YES,AIN1 divider lower
C101,1,"100nF ADC filter",Murata,GRM188R71C104KA01D,0603,YES,ADC_IN1 filter
TVS12,1,AIN2 low-leakage ESD,Nexperia,"PESD3V3L1BA,115",SOD323,YES,"At connector"
R102,1,10.0k 1% AIN series,Yageo,RC0603FR-0710KL,0603,YES,AIN2 divider upper
R112,1,15.0k 1% AIN lower,Yageo,RC0603FR-0715KL,0603,YES,AIN2 divider lower
C102,1,"100nF ADC filter",Murata,GRM188R71C104KA01D,0603,YES,ADC_IN2 filter
TVS13,1,AIN3 low-leakage ESD,Nexperia,"PESD3V3L1BA,115",SOD323,YES,"At connector"
R103,1,10.0k 1% AIN series,Yageo,RC0603FR-0710KL,0603,YES,AIN3 divider upper
R113,1,15.0k 1% AIN lower,Yageo,RC0603FR-0715KL,0603,YES,AIN3 divider lower
C103,1,"100nF ADC filter",Murata,GRM188R71C104KA01D,0603,YES,ADC_IN3 filter
TVS14,1,AIN4 low-leakage ESD,Nexperia,"PESD3V3L1BA,115",SOD323,YES,"At connector"
R104,1,10.0k 1% AIN series,Yageo,RC0603FR-0710KL,0603,YES,AIN4 divider upper
R114,1,15.0k 1% AIN lower,Yageo,RC0603FR-0715KL,0603,YES,AIN4 divider lower
C104,1,"100nF ADC filter",Murata,GRM188R71C104KA01D,0603,YES,ADC_IN4 filter
TVS15,1,AIN5 low-leakage ESD,Nexperia,"PESD3V3L1BA,115",SOD323,YES,"At connector"
R105,1,10.0k 1% AIN series,Yageo,RC0603FR-0710KL,0603,YES,AIN5 divider upper
R115,1,15.0k 1% AIN lower,Yageo,RC0603FR-0715KL,0603,YES,AIN5 divider lower
C105,1,"100nF ADC filter",Murata,GRM188R71C104KA01D,0603,YES,ADC_IN5 filter
TVS16,1,AIN6 low-leakage ESD,Nexperia,"PESD3V3L1BA,115",SOD323,YES,"At connector"
R106,1,10.0k 1% AIN series,Yageo,RC0603FR-0710KL,0603,YES,AIN6 divider upper
R116,1,15.0k 1% AIN lower,Yageo,RC0603FR-0715KL,0603,YES,AIN6 divider lower
C106,1,"100nF ADC filter",Murata,GRM188R71C104KA01D,0603,YES,ADC_IN6 filter
TVS17,1,AIN7 low-leakage ESD,Nexperia,"PESD3V3L1BA,115",SOD323,YES,"At connector"
R107,1,10.0k 1% AIN series,Yageo,RC0603FR-0710KL,0603,YES,AIN7 divider upper
R117,1,15.0k 1% AIN lower,Yageo,RC0603FR-0715KL,0603,YES,AIN7 divider lower
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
